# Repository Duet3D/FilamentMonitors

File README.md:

# Duet3D Filament monitor hardware source files:

2 Variations:

## Magnetic Filament Monitor

https://www.duet3d.com/magneticfilamentmonitor

Documentation:
https://docs.duet3d.com/Duet3D_hardware/Accessories/Rotating_Magnet_Filament_Monitor

## Laser Filament Monitor
_This is no longer produced_

Documentation for reference:
https://docs.duet3d.com/Duet3D_hardware/Accessories/Laser_Filament_Monitor

## Support requests

Please use the [forum](https://forum.duet3d.com) for support requests.

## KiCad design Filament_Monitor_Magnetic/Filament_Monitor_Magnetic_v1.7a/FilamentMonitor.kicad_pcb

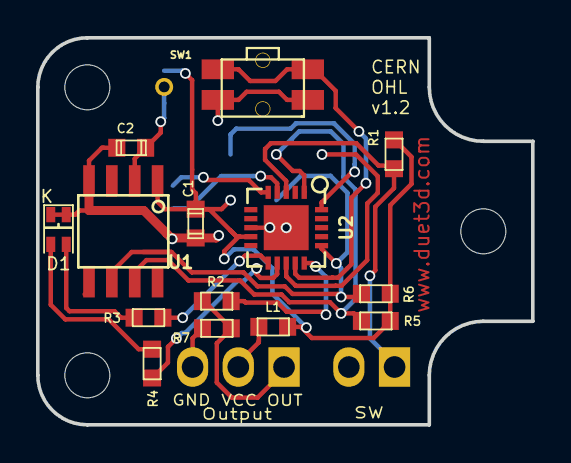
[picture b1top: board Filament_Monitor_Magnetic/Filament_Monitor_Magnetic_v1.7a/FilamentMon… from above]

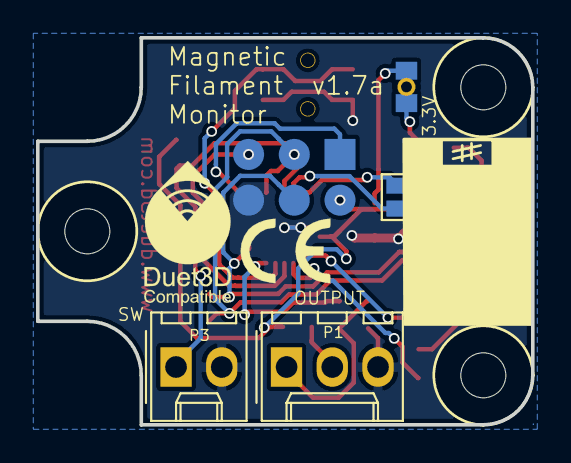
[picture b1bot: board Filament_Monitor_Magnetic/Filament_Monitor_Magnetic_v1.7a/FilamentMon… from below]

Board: 2 copper layers, 27.5 x 21.5 mm, 24 parts (10 on the bottom side), 18 nets.

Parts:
C1: 100n; C_0603
C2: 1u; C_0603
D1: Led_2x2; 2x2_SMD_LED_1.6x1.25mm
JP1: 3.3V; SJ_Bridged
L1: 220R @100Mhz; R_0603
M1: Logo; LOGO_Duet3dCompatible_xs
M2, M4, M5: MH 2.5mm; Fixing_M2.5_clearance_5.5
M6: Logo CE; Logo_CE_Tiny_mirror
P1: OUTPUT; Molex_KK-254_AE-6410-03A_1x03_P2.54mm_Vertical
P2: Prog - DNP; Test_Point_2x3
P3: SW; Molex_KK-254_AE-6410-02A_1x02_P2.54mm_Vertical
P4: M2; SJ
R1, R5, R6: 4K7; R_0603
R2: 330R; R_0603
R3, R4: 470R; R_0603
R7: 100K; R_0603
SW1: Push; SW_SIDE_1_lugs
U1: AS5601; SOIC-8
U2: ATtiny44A-MFR / ATtiny44A-MUR; QFN-20-1EP_4x4mm_P0.5mm_EP2.5x2.5mm

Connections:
GND: C1.2, C2.2, D1.2, D1.4, P1.3, P2.6, P3.2, R7.1, SW1.2, U1.4, U2.8, U2.21
MISO: P2.1, U2.20
unnamed: C2.1, JP1.1, U1.2
unnamed: D1.1, R3.2
unnamed: D1.3, R4.2
unnamed: L1.2, P1.2
unnamed: P3.1, R1.2, U2.3
unnamed: R2.1, U2.15
unnamed: R3.1, U2.11
unnamed: R4.1, U2.12
unnamed: SW1.1, U2.14
OUT: P1.1, R2.2, R7.2
PA0: P4.2, U2.5
PA1: P4.1, U2.4
RST: P2.5, U2.13
SCL: P2.3, R5.2, U1.7, U2.1
SDA/MOSI: P2.4, R6.2, U1.6, U2.16
VCC: C1.1, JP1.2, L1.1, P2.2, R1.1, R5.1, R6.1, U1.1, U2.9

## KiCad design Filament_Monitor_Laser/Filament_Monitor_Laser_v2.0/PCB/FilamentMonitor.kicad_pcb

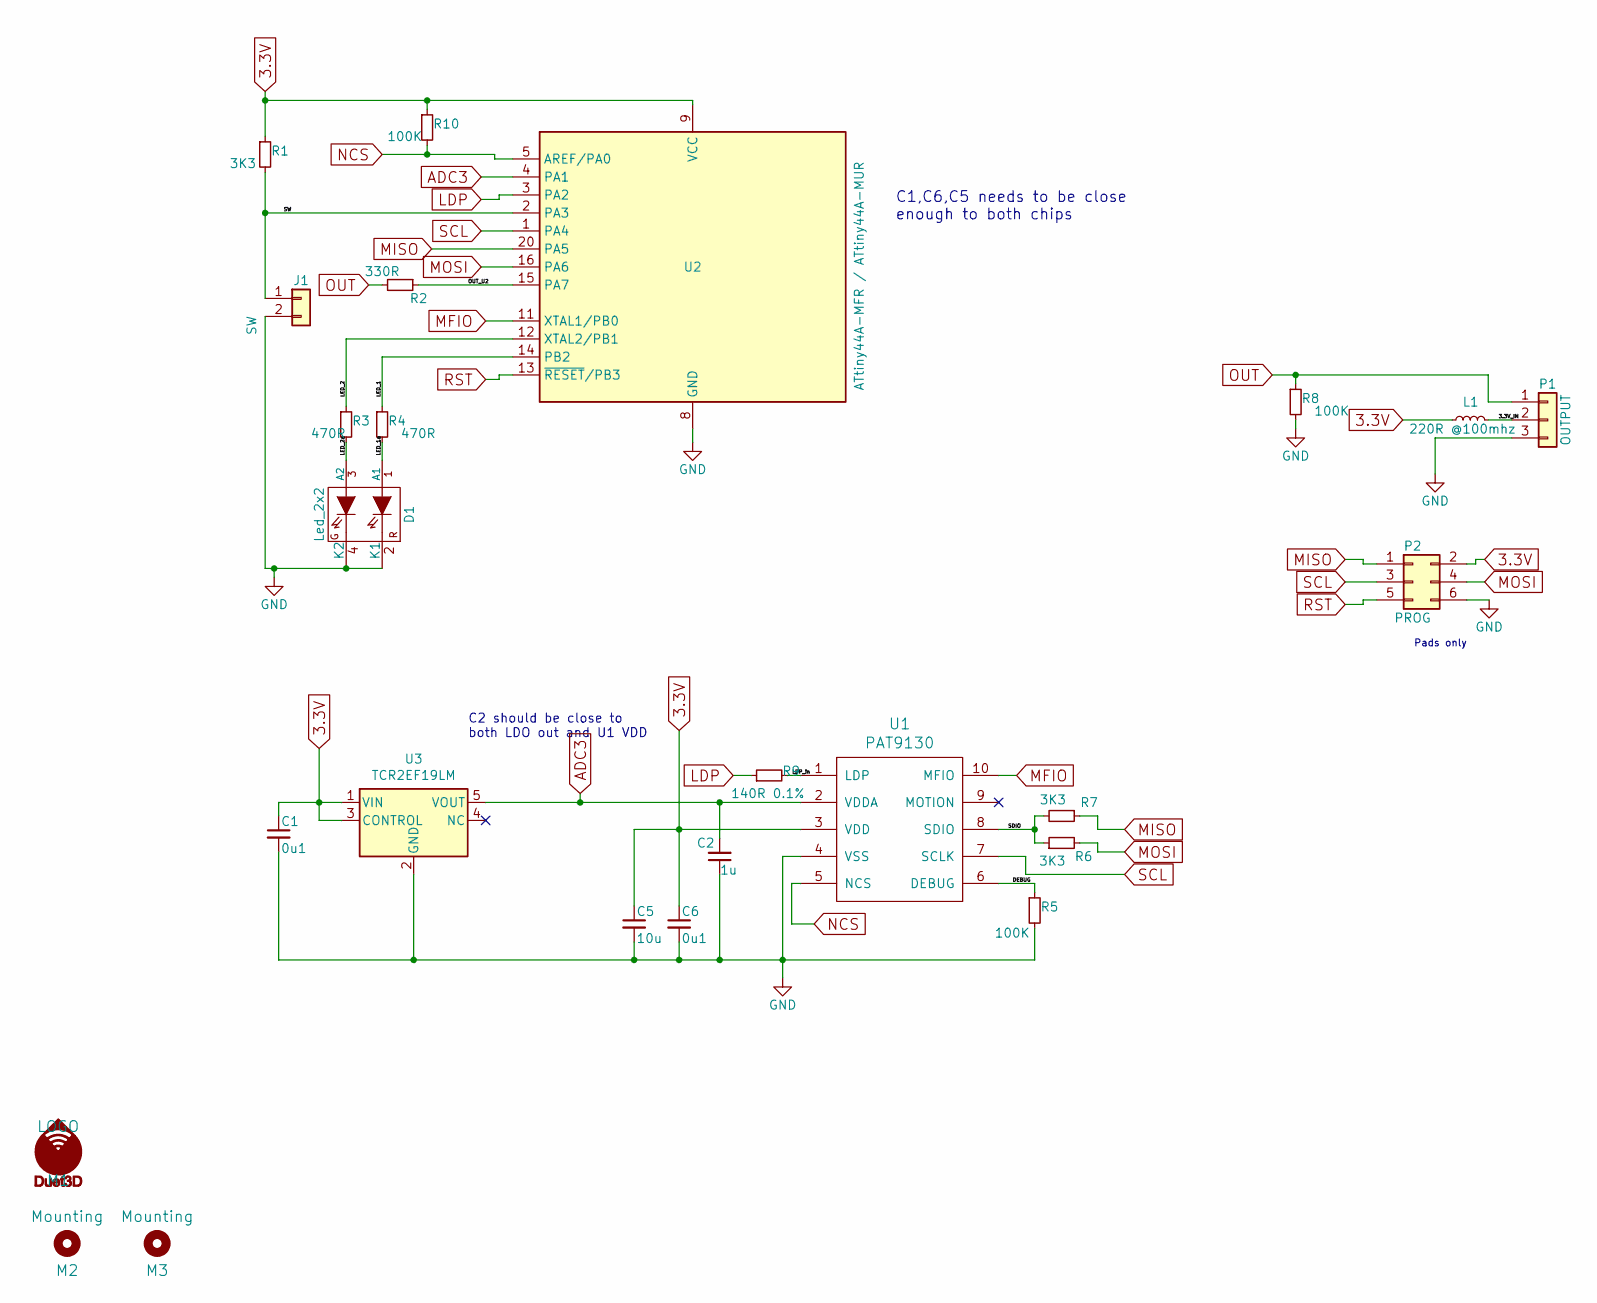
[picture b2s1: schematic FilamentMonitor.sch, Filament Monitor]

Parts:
C1, C6: 0u1; C_0603
C2: 1u; C_0805
C5: 10u; C_0805
D1: Led_2x2; 2x2_SMD_LED_1.6x1.25mm
J1: SW; PIN_ARRAY_2X1
L1: 220R @100mhz; R_0603
M1: LOGO; LOGO_Duet3dCompatible
M2, M3: Mounting; MountingHole_2.9mm
P1: OUTPUT; PIN_ARRAY_3X1
P2: PROG; Test_Point_2x3
R1, R6, R7: 3K3; R_0603
R2: 330R; R_0603
R3, R4: 470R; R_0603
R5, R8, R10: 100K; R_0603
R9: 140R 0.1%; R_0603
U1: PAT9130
U2: ATtiny44A-MFR / ATtiny44A-MUR; QFN-20-1EP_4x4mm_Pitch0.5mm
U3: TCR2EF19LM; SOT-23-5

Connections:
3.3V: C1.1, C5.1, C6.1, L1.1, P2.2, R1.1, R10.1, U1.3 (VDD), U2.9 (VCC), U3.1 (VIN), U3.3 (CONTROL)
/3.3V_IN: L1.2, P1.2
/DEBUG: R5.1, U1.6 (DEBUG)
/LDP_in: R9.2, U1.1 (LDP)
/LED_1: R4.1, U2.14 (PB2)
/LED_1a: D1.1 (A1), R4.2
/LED_2: R3.1, U2.12 (XTAL2/PB1)
/LED_2a: D1.3 (A2), R3.2
/OUT_U2: R2.1, U2.15 (PA7)
/SDIO: R6.1, R7.2, U1.8 (SDIO)
/SW: J1.1, R1.2, U2.2 (PA3)
ADC3: C2.2, U1.2 (VDDA), U2.4 (PA1), U3.5 (VOUT)
GND: C1.2, C2.1, C5.2, C6.2, D1.2 (K1), D1.4 (K2), J1.2, P1.3, P2.6, R5.2, R8.2, U1.4 (VSS), U2.8 (GND), U2.21 (GND), U3.2 (GND)
LDP: R9.1, U2.3 (PA2)
MFIO: U1.10 (MFIO), U2.11 (XTAL1/PB0)
MISO: P2.1, R7.1, U2.20 (PA5)
MOSI: P2.4, R6.2, U2.16 (PA6)
NCS: R10.2, U1.5 (NCS), U2.5 (AREF/PA0)
OUT: P1.1, R2.2, R8.1
RST: P2.5, U2.13 (~RESET~/PB3)
SCL: P2.3, U1.7 (SCLK), U2.1 (PA4)

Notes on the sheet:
Pads only
C1,C6,C5 needs to be close enough to both chips
C2 should be close to both LDO out and U1 VDD

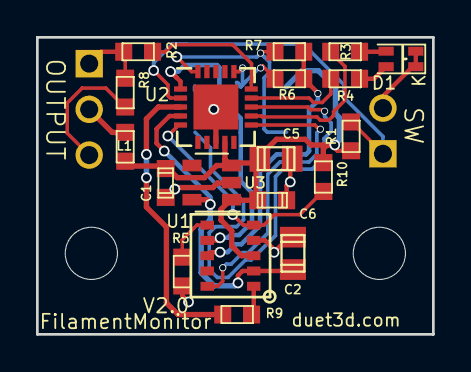
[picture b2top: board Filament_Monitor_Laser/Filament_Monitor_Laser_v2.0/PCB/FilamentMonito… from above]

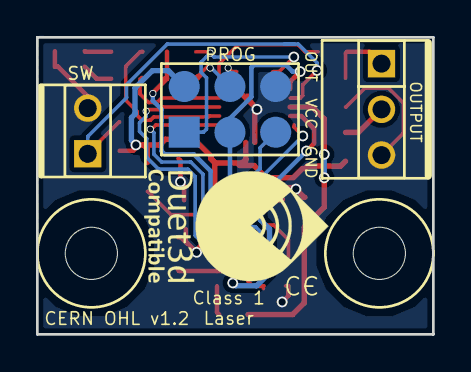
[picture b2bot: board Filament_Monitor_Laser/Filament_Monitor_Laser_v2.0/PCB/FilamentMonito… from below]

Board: 2 copper layers, 22.0 x 16.5 mm, 25 parts (6 on the bottom side), 21 nets.

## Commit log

2018-11-01 Update LICENSE
2018-11-01 Laser Filament Monitor KiCAD Project
    See https://duet3d.dozuki.com/Wiki/Duet3dFilamentMonitor_LaserVersion
2019-04-26 Added new housing
    for LFM v2.0
2019-10-04 Added Magnetic Filament Monitor
    KiCad Source
2019-10-04 Magnet Filament Monitor enclosure
2020-04-21 typos
2020-04-21 Added enclosure step files
2020-04-22 Added the IC3D 2.85mm housing
2021-03-21 Added V2.0 KiCAD source
2021-09-01 Directory reorganisation
2021-09-01 Added 1.7a info
2021-09-27 Added enclosure v2 STLs
2021-09-27 M3 clearance version of the enclosure body
2021-11-13 added a zip file of the three stls
2021-11-13 Updated readme and added zip for enclosure v2
2022-12-02 Added the version 3 enclosure
2022-12-02 added the body version with m3 clearance mounting holes.
2023-02-03 v1.7b added
2025-02-22 add assembled STEP

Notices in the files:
Filament_Monitor_Laser/Filament_Monitor_Laser_v2.0/PCB/FilamentMonitor.kicad_pcb:
CERN OHL v1.2
Filament_Monitor_Magnetic/Filament_Monitor_Magnetic_v1.7/FilamentMonitor.sch:
see License.md for licensing information
Filament_Monitor_Magnetic/Filament_Monitor_Magnetic_v1.7a/FilamentMonitor.kicad_pcb:
CERN OHL 1.2
